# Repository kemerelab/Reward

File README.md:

Open Source Design for Liquid Reward in Rodent Behavioral Mazes
======

These reward wells are meant to be installed at the ends of a track. When the animal's breaks the infra-red beam at the right
location, liquid reward is delivered either via a pump or valve-controlled gravity-feed system when the animal. 

### Manufacturing
Designs are provided to 3D print the reward well. We have had success with Shapeways "White Strong and Flexible", as well as
printing in-house on our Afinia 3D printer. To prepare the food well, feed wires through the structure of the food well and
solder them to a 5 mm IR LED (e.g., [Digikey part 751-1210](https://www.digikey.com/product-detail/en/vishay-semiconductor-opto-division/TSHF5210/751-1210-ND/1681345)) and a 5 mm IR phototransistor 
(e.g., [Digikey part 475-1080](http://www.digikey.com/short/7zhpv2)). These wires are sheathed in a thick heatshrink to protect them from being eaten and then then soldered to the interface board. After testing for functionality, we expoy the LED and phototransistor into place. We additionally install a luer connection (Value Plastics [KTFLL-1](http://www.nordsonmedical.com/technical/part_drawings/KFTLL.pdf)) into the liquid feed hole at the bottom of the well.

We have ordered interface boards to be manufactured by Seeed Studio, using their PCBA service, at a cost of ~$2/unit.

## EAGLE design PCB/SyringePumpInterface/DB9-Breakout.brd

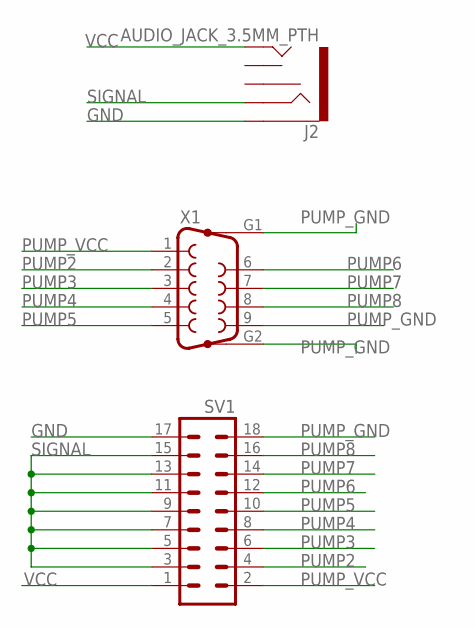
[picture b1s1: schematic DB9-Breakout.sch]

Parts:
J2: AUDIO_JACK_3.5MM_PTH; AUDIO-JACK
SV1: MA09-2
X1: F09HP

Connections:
GND: J2.SLEEVE, SV1.17
PUMP2: SV1.4, X1.2
PUMP3: SV1.6, X1.3
PUMP4: SV1.8, X1.4
PUMP5: SV1.10, X1.5
PUMP6: SV1.12, X1.6
PUMP7: SV1.14, X1.7
PUMP8: SV1.16, X1.8
PUMP_GND: SV1.18, X1.9, X1.G1, X1.G2
PUMP_VCC: SV1.2, X1.1
SIGNAL: J2.RING, SV1.3, SV1.5, SV1.7, SV1.9, SV1.11, SV1.13, SV1.15
VCC: J2.TIP, SV1.1

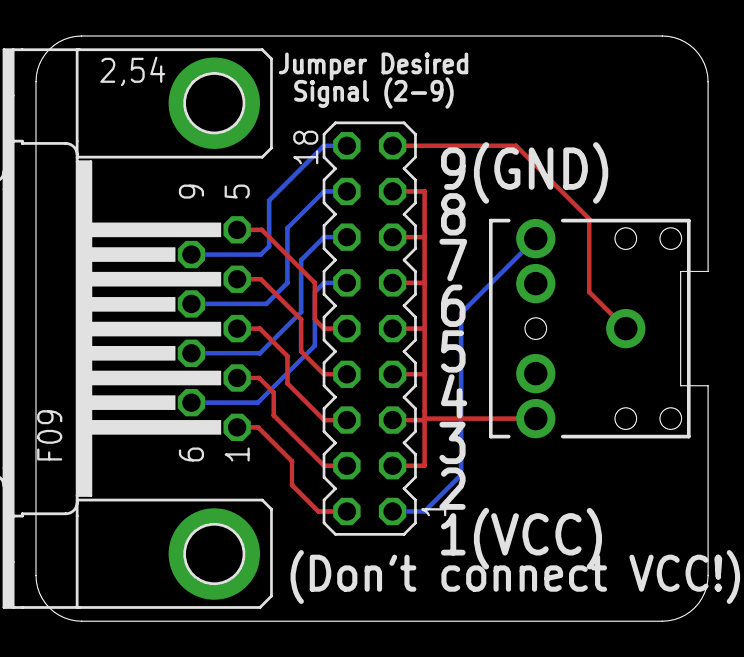
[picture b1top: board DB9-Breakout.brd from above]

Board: 2 copper layers, 37.3 x 32.5 mm, 3 parts (0 on the bottom side), 12 nets.

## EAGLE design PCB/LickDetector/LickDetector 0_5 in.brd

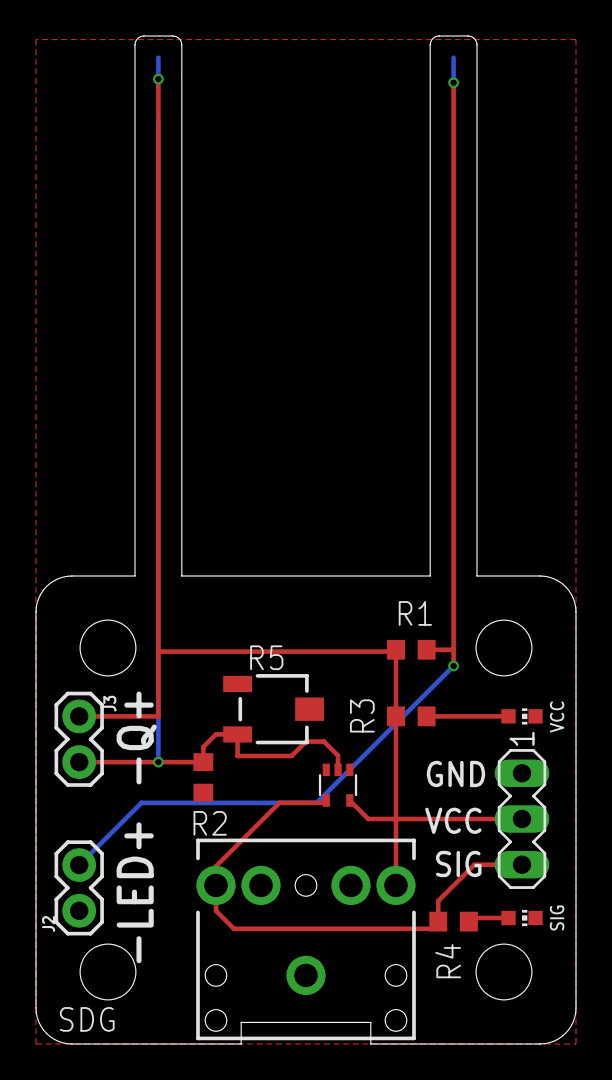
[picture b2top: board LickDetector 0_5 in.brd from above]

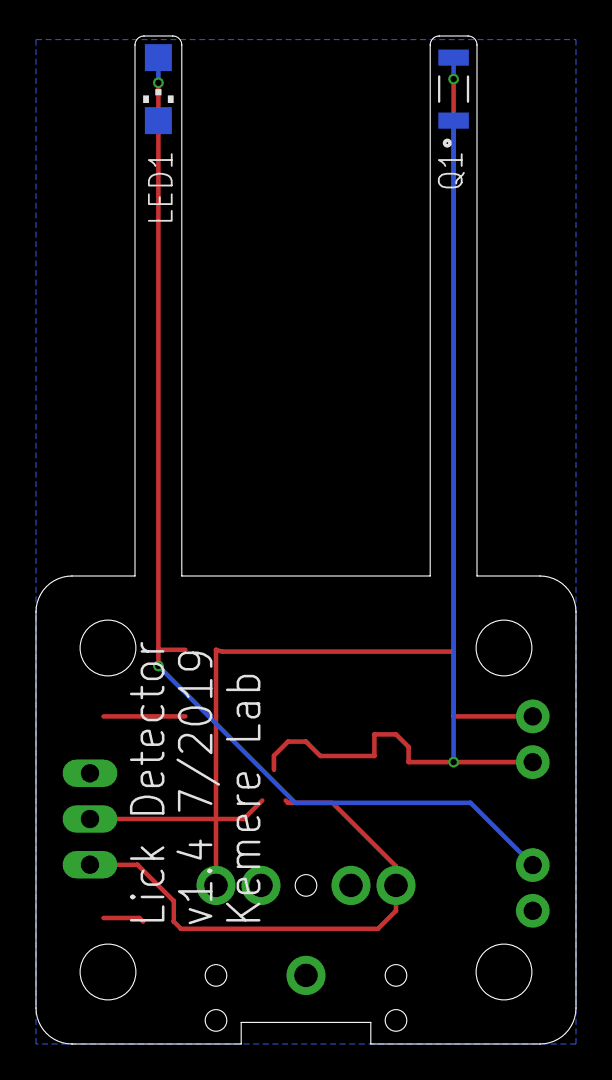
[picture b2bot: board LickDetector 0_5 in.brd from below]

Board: 2 copper layers, 30.0 x 56.0 mm, 14 parts (2 on the bottom side), 7 nets.

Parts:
IC1: 74AHC1G14DCK; SC70-5
J1: AUDIO_JACK_3.5MM_PTH; AUDIO-JACK
J2, J3: 1X02
LED1: CHIPLED_1206
PWR: CHIP-LED0603
Q1: SFH_3015_FA; XDCR_SFH_3015_FA
R1, R2, R3, R4: R0603
R5: 3223J
SIG: CHIP-LED0603
SV1: MA03-1

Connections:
GND: IC1.3, J1.SLEEVE, J2.1, LED1.C, PWR.C, R2.1, R5.2, SIG.C, SV1.1
LEDCATHODE: J2.2, LED1.A, R1.1
unnamed: PWR.A, R3.2
unnamed: R4.2, SIG.A
PHOTOTRANS: IC1.2, J3.2, Q1.1, R2.2, R5.3
SIGNAL: IC1.4, J1.RING, R4.1, SV1.3
VCC: IC1.5, J1.TIP, J3.1, Q1.2, R1.2, R3.1, SV1.2

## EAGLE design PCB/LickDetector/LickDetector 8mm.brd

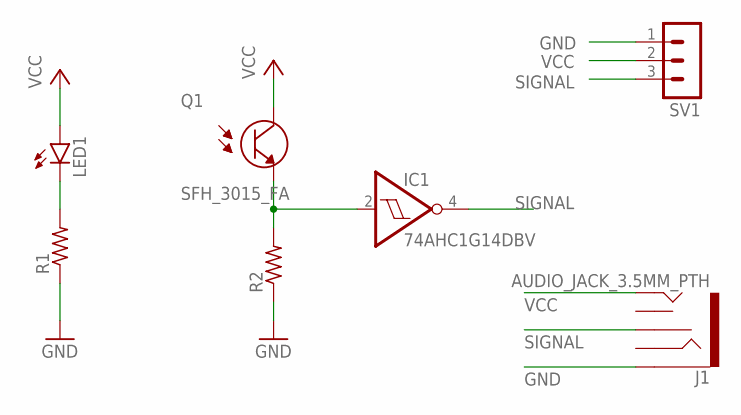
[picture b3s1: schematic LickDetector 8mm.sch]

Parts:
IC1: 74AHC1G14DBV; SOT23-5
J1: AUDIO_JACK_3.5MM_PTH; AUDIO-JACK
LED1: LEDCHIPLED_1206; CHIPLED_1206
Q1: SFH_3015_FA; XDCR_SFH_3015_FA
R1, R2: R-US_M1206; M1206
SV1: MA03-1

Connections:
GND: IC1.3 (GND), J1.SLEEVE, R1.1, R2.1, SV1.1
unnamed: LED1.C, R1.2
unnamed: IC1.2 (I), Q1.1 (E), R2.2
SIGNAL: IC1.4 (O), J1.RSH, SV1.3
VCC: IC1.5 (VCC), J1.TIP, LED1.A, Q1.2 (C), SV1.2

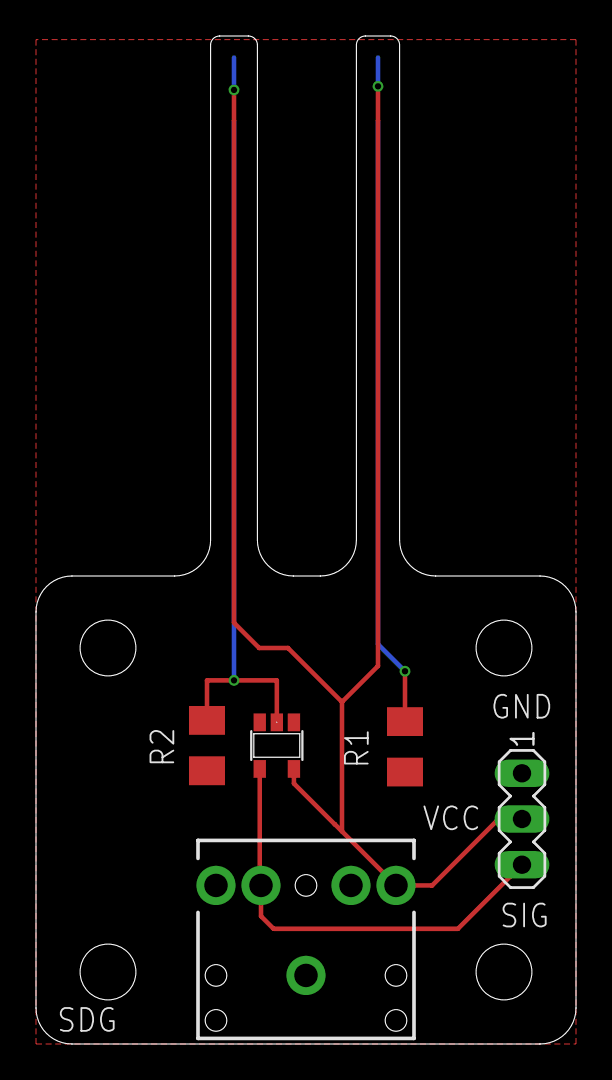
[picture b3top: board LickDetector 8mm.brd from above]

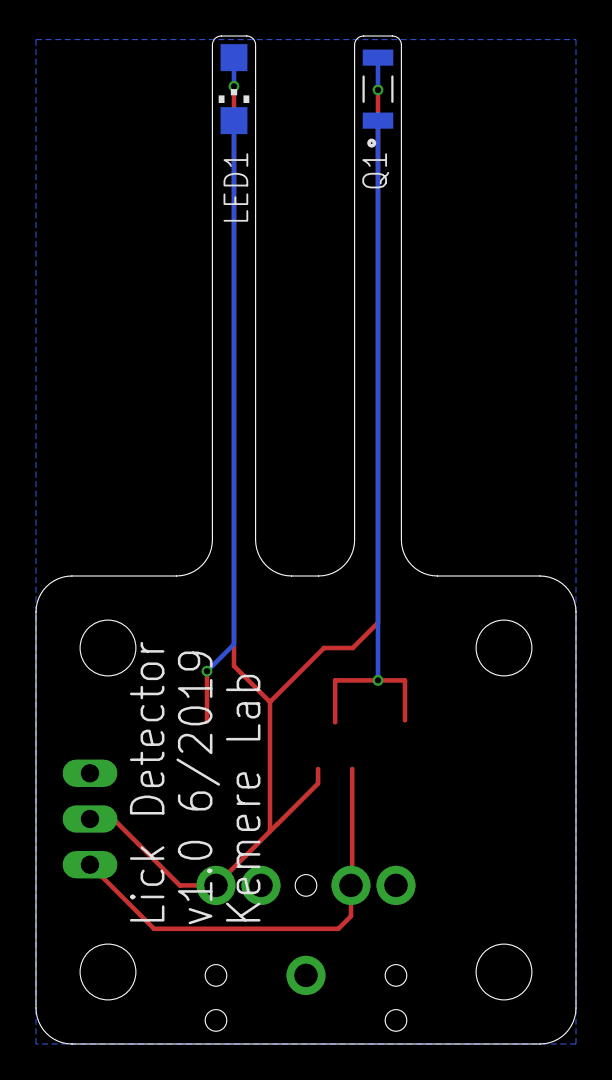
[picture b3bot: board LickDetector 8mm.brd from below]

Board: 2 copper layers, 30.0 x 56.0 mm, 7 parts (2 on the bottom side), 5 nets.

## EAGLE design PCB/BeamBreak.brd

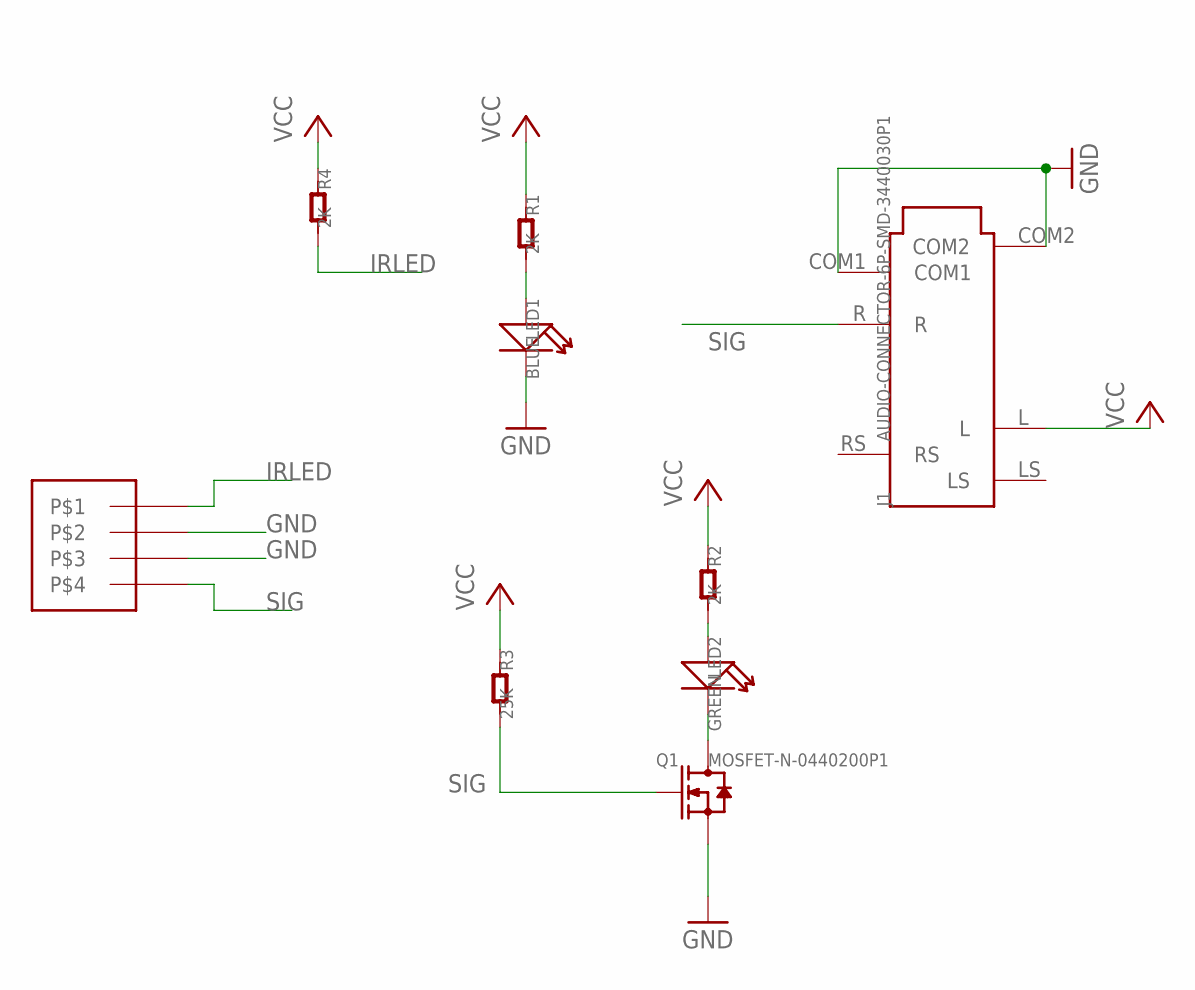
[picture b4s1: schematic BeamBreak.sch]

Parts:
J1: AUDIO-CONNECTOR-6P-SMD-3440030P1; 6P-SMD-3.5
LED1: BLUE; LED0603
LED2: GREEN; LED0603
Q1: MOSFET-N-0440200P1; SOT23
R1, R2, R4: 2K; R0603
R3: 25K; R0603
U$1: HO4; H04

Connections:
GND: J1.COM1, J1.COM2, LED1.-, Q1.2 (S), U$1.2, U$1.3
IRLED: R4.2, U$1.1
unnamed: LED2.+, R2.2
unnamed: LED2.-, Q1.3 (D)
unnamed: LED1.+, R1.2
SIG: J1.R, Q1.1 (G), R3.2, U$1.4
VCC: J1.L, R1.1, R2.1, R3.1, R4.1

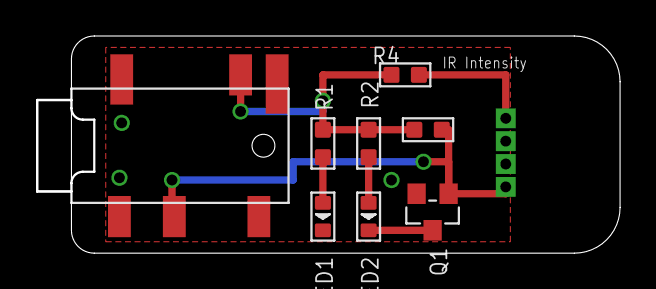
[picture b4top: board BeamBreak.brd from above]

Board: 2 copper layers, 32.3 x 11.9 mm, 9 parts (0 on the bottom side), 7 nets.

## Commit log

2014-12-16 Initial commit. Added PCB and SolidWorks files
2014-12-16 Added a picture
2014-12-16 Update README.md
    added link to value plastics part
2014-12-16 Update README.md
    Fixed link
2015-01-07 Changed connections for wires to a header so that solder mask will be properly applied.
2018-08-28 added linear track arduino controller code
2018-08-28 added w maze arduino controller code
2019-01-07 Updated link that used to be dead
2019-01-17 Added BOM for easier tracking of parts
2019-06-25 Added a bunch more designs
2019-06-26 Added long-narrow beam break PCBs in different sizes.
2019-06-26 Added side-view LED datasheet for lick detector PCB.
2019-06-26 Added datasheet for 74AHC1G14GW inverting schmitt trigger.
2019-07-10 Added power and signal LEDs to Lick Detector beam break PCB
2019-07-10 Added DB9 syringe pump board with jumper header for flexibility
2020-03-11 Fixed bug where wrong audio jack pin was connected for signal. Also added cuttout for jack and potentiometer
2020-07-23 New mouse-scale nose poke foodwell designs added. Also a flexible PCB beam break pcb. Also updated DB9 breakout for the syringe pump that has a jumper to choose the pulse pin.

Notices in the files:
parts and their libraries:
SparkFun-Connectors: Licensing: Creative Commons ShareAlike 4.0 International - https://creativecommons.org/licenses/by-sa/4.0
